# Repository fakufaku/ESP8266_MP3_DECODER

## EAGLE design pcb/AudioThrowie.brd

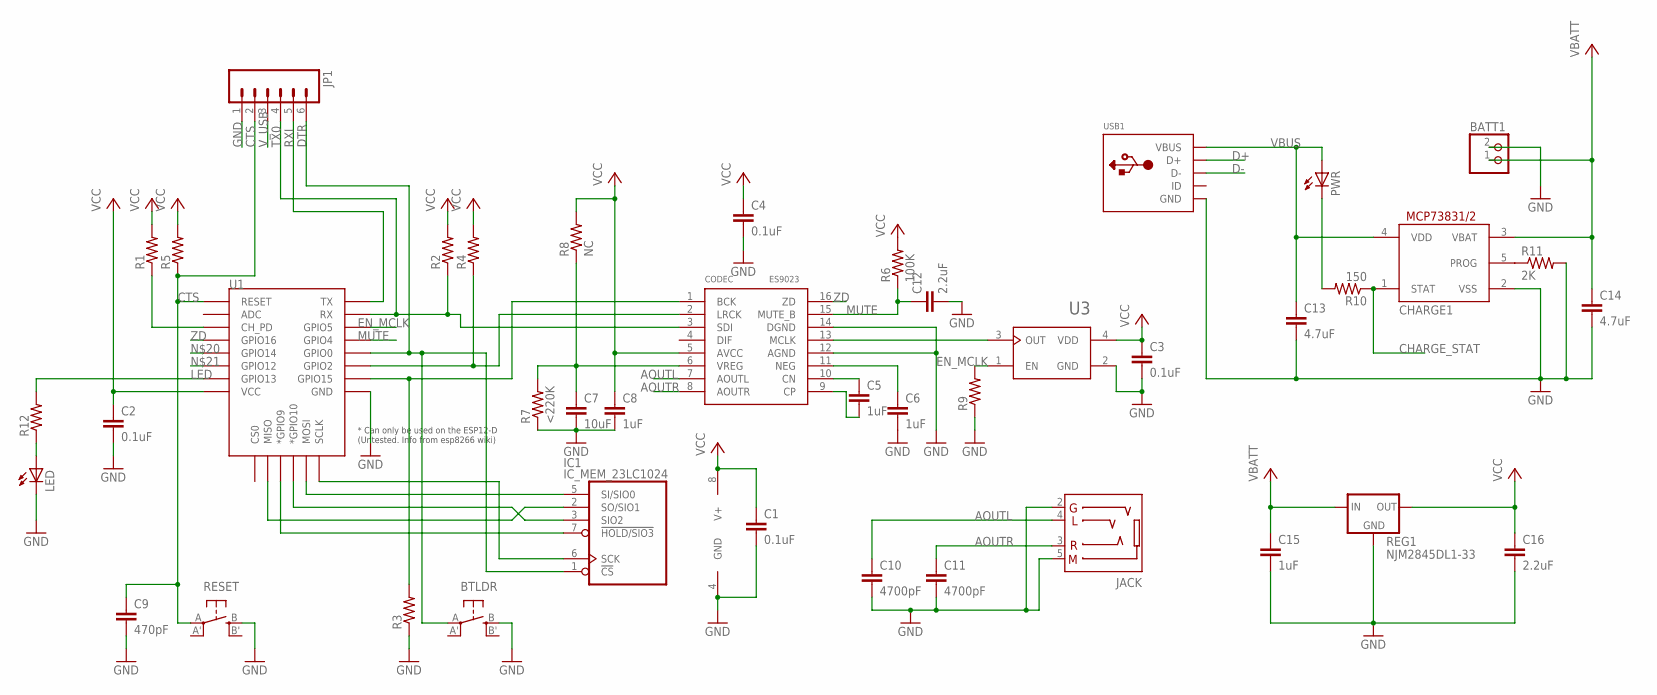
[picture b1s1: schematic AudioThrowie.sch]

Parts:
BATT1: JST_2PIN-THM; JST-PH-2-THM
BTLDR: SPST_TACT-EVQQ2; EVQ-Q2
C1, C2, C3, C4: 0.1uF; 0805
C5, C6, C8, C15: 1uF; 0805
C7: 10uF; 0805
C9: 470pF; 0805
C10, C11: 4700pF; 0805
C12, C16: 2.2uF; 0805
C13, C14: 4.7uF; 0805
CHARGE1: MCP73831/OT; SOT23-5L
CODEC: ES9023; SOP16
IC1: IC_MEM_23LC1024; SOIC-8
JACK: AUDIO-STEREO-JACK-3.5MM-4SLEEVES; PJ320D
JP1: M06LONGPADS; 1X06_LONGPADS
LED: LED3MM
PWR: LED3MM
R1, R2, R3, R4, R5, R9, R12: R-US_M0805; M0805
R6: 100K; M0805
R7: <220K; M0805
R8: NC; M0805
R10: 150; R0805
R11: 2K; R0603
REG1: NJM2845DL1-33; DPACK
RESET: SPST_TACT-EVQQ2; EVQ-Q2
U1: ESP12ESMD; ESP12E-SMD
U3: OSCILLATOR-AW-2.5X2; AW-CRYSTAL-2.5X2
USB1: USBMINIB; USB-MINIB

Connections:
AOUTL: C10.1, CODEC.7 (AOUTL), JACK.4 (TIP)
AOUTR: C11.1, CODEC.8 (AOUTR), JACK.3 (RING1)
CHARGE_STAT: CHARGE1.1 (STAT), R10.1
CTS: C9.1, JP1.2, R5.1, RESET.A, U1.RESET
D+: USB1.D+
D-: USB1.D-
DTR: BTLDR.A, IC1.1 (!CS), JP1.6, U1.GPIO0
EN_MCLK: R9.2, U1.GPIO5, U3.1 (EN)
GND: BATT1.2 (1), BTLDR.B (S), C1.2, C2.2, C3.2, C4.2, C6.2, C7.2, C8.2, C9.2, C10.2, C11.2, C12.2, C13.2, C14.2, C15.2, C16.2, CHARGE1.2 (VSS), CODEC.12 (AGND), CODEC.14 (DGND), IC1.4 (GND), JACK.2 (RING2), JACK.5 (SLEEVE), JP1.1, LED.K (C), R3.1, R7.1, R9.1, R11.2, REG1.4 (GND), RESET.B (S), U1.GND, U3.2 (GND), USB1.GND
LED: R12.2, U1.GPIO13
MUTE: C12.1, CODEC.15 (MUTE_B), R6.1, U1.GPIO4
unnamed: C5.1, CODEC.10 (CN)
unnamed: IC1.2 (SO/SIO1), U1.MISO
unnamed: IC1.3 (SIO2), U1.GPIO10 (*GPIO10)
unnamed: IC1.5 (SI/SIO0), U1.MOSI
unnamed: IC1.6 (SCK), U1.SCLK
unnamed: IC1.7 (!HOLD/SIO3), U1.GPIO9 (*GPIO9)
unnamed: CODEC.2 (LRCK), R4.1, U1.GPIO2
unnamed: C5.2, CODEC.9 (CP)
unnamed: CODEC.1 (BCK), R3.2, U1.GPIO15
unnamed: CODEC.13 (MCLK), U3.3 (OUT)
unnamed: C6.1, CODEC.11 (NEG)
unnamed: R1.1, U1.CH_PD
unnamed: PWR.K (C), R10.2
unnamed: CHARGE1.5 (PROG), R11.1
unnamed: C7.1, CODEC.6 (VREG), R7.2, R8.1
unnamed: LED.A, R12.1
RXI: JP1.5, U1.TXD0 (TX)
TX0: CODEC.3 (SDI), JP1.4, R2.1, U1.RXD0 (RX)
VBATT: BATT1.1 (2), C14.1, C15.1, CHARGE1.3 (VBAT), REG1.1 (IN)
VBUS: C13.1, CHARGE1.4 (VDD), PWR.A, USB1.VBUS
VCC: C1.1, C2.1, C3.1, C4.1, C8.1, C16.1, CODEC.5 (AVCC), IC1.8 (V+), R1.2, R2.2, R4.2, R5.2, R6.2, R8.2, REG1.3 (OUT), U1.VCC, U3.4 (VDD)
V_USB: JP1.3
ZD: CODEC.16 (ZD), U1.GPIO16

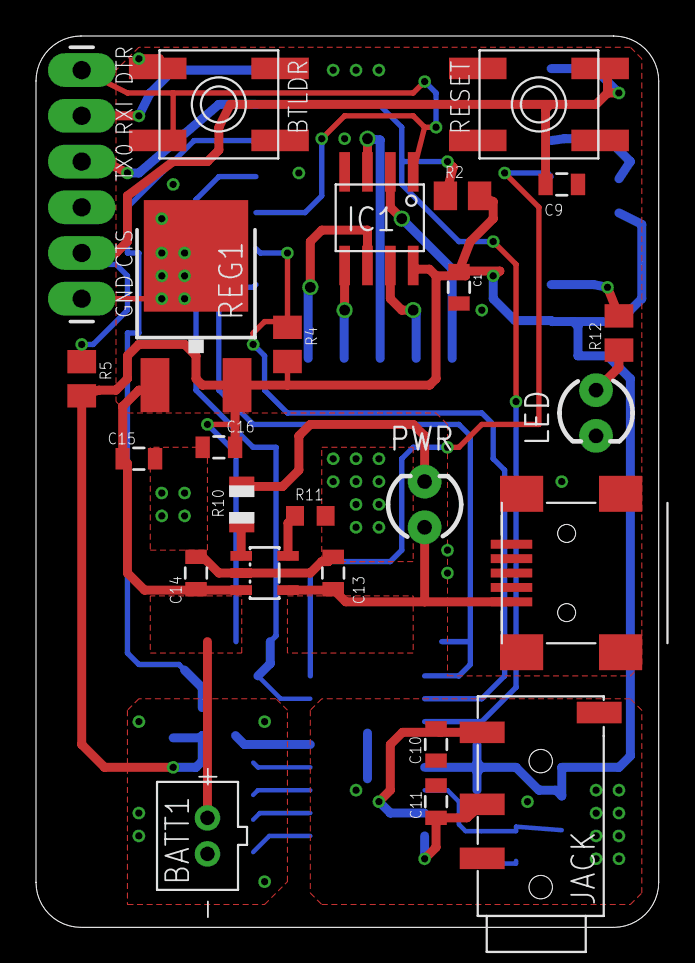
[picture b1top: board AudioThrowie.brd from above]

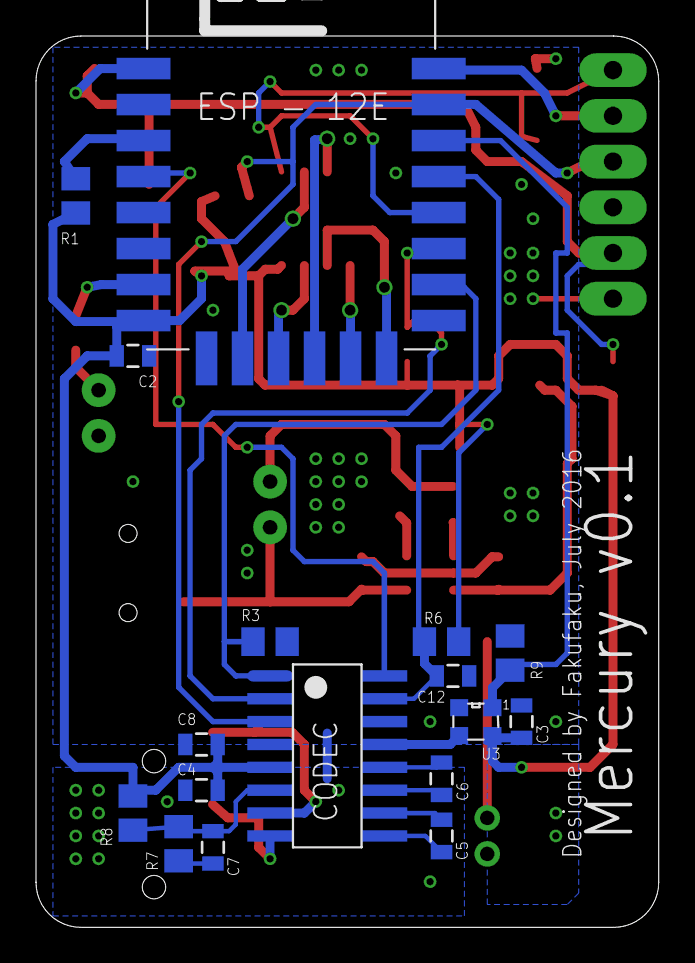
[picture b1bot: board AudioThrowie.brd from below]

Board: 2 copper layers, 34.6 x 49.5 mm, 42 parts (17 on the bottom side), 31 nets.

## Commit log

2016-09-07 Custimisation
2016-09-07 Added Eagle CAD files for the PCB.
